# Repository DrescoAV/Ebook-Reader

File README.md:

# OpenBook Reader  
**Autor:** Andrei-Valerian Andreescu  
**Grupa:** 335CC  

## Diagrama bloc

---

## Bill Of  Materials (BOM)
| Component Name                            | Link                                                                                                   | Datasheet Link                                                                                           |
|------------------------------------------|-------------------------------------------------------------------------------------------------------------|-----------------------------------------------------------------------------------------------------------|
| 112ATAARR03ATTEND                        | [Link](https://store.comet.srl.ro/Catalogue/Product/43497/)                                                 | [Link](https://www.attend.com.tw/data/download/file/112A-TAAR-R03.rar)                                   |
| ADAFRUIT_CHIP-LED0603                    | [Link](https://www.snapeda.com/parts/KP-1608SURCK/Kingbright/view-part/?ref=search&t=LED%200603)            | [Link](https://www.snapeda.com/parts/KP-1608SURCK/Kingbright/datasheet/)                                 |
| CAPCP3225X100N                           | [Link](https://www.snapeda.com/parts/CPH3225A/Seiko+Instruments/view-part/?ref=eda)                         | [Link](https://www.snapeda.com/parts/CPH3225A/Seiko%20Instruments/datasheet/)                            |
| DIOC1608X36N                             | [Link](https://www.snapeda.com/parts/PGB1010603MR/Littelfuse/view-part/?ref=eda)                            | [Link](https://www.snapeda.com/parts/PGB1010603MR/Littelfuse%20Inc./datasheet/)                          |
| EAGLE-LTSPICE_C0402                      | [Link](https://componentsearchengine.com/part-view/CC0402MRX5R5BB106/YAGEO)                                 | [Link](https://componentsearchengine.com/Datasheets/2/CC0402MRX5R5BB106.pdf)                              |
| ESP32_WROVER_AVX---SD0805S020S1R0_AVX_0  | [Link](https://ro.mouser.com/ProductDetail/KYOCERA-AVX/SD0805S020S1R0?qs=jCA%252BPfw4LHbpkAoSnwrdjw%3D%3D)  | [Link](https://ro.mouser.com/datasheet/2/40/schottky-3165252.pdf)                                        |
| ESP32_WROVER_BME680_PSON80P300X300X100-8N| [Link](https://www.snapeda.com/parts/BME680/Bosch/view-part/?welcome=home)                                  | [Link](https://www.snapeda.com/parts/BME680/Bosch%20Sensortec/datasheet/)                                |
| ESP32_WROVER_EAGLE-LTSPICE_C0402         | [Link](https://componentsearchengine.com/part-view/CC0402MRX5R5BB106/YAGEO)                                 | [Link](https://componentsearchengine.com/Datasheets/2/CC0402MRX5R5BB106.pdf)                              |
| ESP32_WROVER_EAGLE-LTSPICE_R0402         | [Link](https://componentsearchengine.com/part-view/R0402%201%25%20100%20K%20(RC0402FR-07100KL)/YAGEO)       | [Link](https://www.yageo.com/upload/media/product/products/datasheet/rchip/PYu-RC_Group_51_RoHS_L_12.pdf)|
| ESP32_WROVER_SPARKFUN-DISCRETESEMI_SOT23-3| [Link](https://componentsearchengine.com/part-view/DMG2305UX-7/Diodes%20Incorporated)                      | [Link](https://www.diodes.com//assets/Datasheets/DMG2305UX.pdf)                                          |
| ESP32_WROVER_SPARKFUN-IC-POWER_SOT23-5   | [Link](https://ro.mouser.com/ProductDetail/Microchip-Technology/MCP73831T-5ACI-OT?qs=hH%252BOa0VZEiAcgAcEkuamXg%3D%3D) | [Link](https://ro.mouser.com/datasheet/2/268/MCP73831_Family_Data_Sheet_DS20001984H-3441711.pdf)         |
| ESP32C6_VARISTOR_CT/CN1812               | [Link](https://ro.mouser.com/ProductDetail/EPCOS-TDK/B72520T0350K062?qs=dEfas%2FXlABIszF52uu7vrg%3D%3D)     | [Link](https://www.tdk-electronics.tdk.com/inf/75/db/CTVS_14/Surge_protection_series.pdf)                |
| FH34SRJ24S05SH99                         | [Link](https://ro.mouser.com/ProductDetail/Hirose-Connector/FH34SRJ-24S-0.5SH99?qs=vcbW%252B4%252BSTIpKBl5ap9J8Fw%3D%3D) | [Link](https://ro.mouser.com/datasheet/2/185/FH34SRJ_24S_0_5SH_99__CL0580_1255_6_99_2DDrawing_0-1615044.pdf)|
| IND_4828-WE-TPC_WRE                      | [Link](https://ro.mouser.com/ProductDetail/Wurth-Elektronik/744043680?qs=PGXP4M47uW6VkZq%252BkzjrHA%3D%3D)  | [Link](https://www.we-online.com/components/products/datasheet/744043680.pdf)                            |
| JST04_1MM_RA                             | [Link](https://ro.mouser.com/ProductDetail/Adafruit/4208?qs=PzGy0jfpSMtbScLbr0L5dw%3D%3D)                   | [Link](https://ro.mouser.com/ProductDetail/Adafruit/4208?qs=PzGy0jfpSMtbScLbr0L5dw%3D%3D)                 |
| MYBUTTON                                 | [Link](https://industry.panasonic.com/global/en/products/control/switch/light-touch/number/evqpuj02k)       | [Link](https://industry.panasonic.com/global/en/downloads?tab=catalog&small_g_cd=203&part_no=EVQPUJ02K)  |
| RCL_CT3528                               | [Link](https://www.snapeda.com/parts/TAJB475K025RNJ/AVX/view-part/?t=capacitor%203528&con_ref=None)         | [Link](https://www.snapeda.com/parts/TAJB475K025RNJ/AVX/datasheet/)                                      |
| SAMACSYS_PARTS_USB4110GFA                | [Link](https://componentsearchengine.com/part-view/USB4110-GF-A/GCT%20(GLOBAL%20CONNECTOR%20TECHNOLOGY))    | [Link](https://gct.co/files/drawings/usb4110.pdf)                                                         |
| SOD3716X135N                             | [Link](https://ro.mouser.com/ProductDetail/KYOCERA-AVX/SD0805S020S1R0?qs=jCA%252BPfw4LHbpkAoSnwrdjw%3D%3D)  | [Link](https://ro.mouser.com/datasheet/2/40/schottky-3165252.pdf)                                        |
| SOIC127P1032X265-16N                     | [Link](https://eu.mouser.com/ProductDetail/Wurth-Elektronik/744043680?qs=PGXP4M47uW6VkZq%252BkzjrHA%3D%3D)  | [Link](https://www.snapeda.com/parts/DS3231SN%23/Analog%20Devices/datasheet/)                            |
| SON127P600X800X80-9N                     | [Link](https://www.snapeda.com/parts/W25Q512JVEIQ/Winbond+Electronics/view-part/?ref=eda)                   | [Link](https://www.snapeda.com/parts/W25Q512JVEIQ/Winbond%20Electronics/datasheet/)                      |
| SON50P200X200X80-9N                      | [Link](https://www.snapeda.com/parts/MAX17048G+T10/Analog+Devices/view-part/?ref=eda)                       | [Link](https://www.snapeda.com/parts/MAX17048G+T10/Analog%20Devices/datasheet/)                          |
| SOT65P210X110-3N                         | [Link](https://componentsearchengine.com/part-view/SI1308EDL-T1-GE3/Vishay)                                 | [Link](https://componentsearchengine.com/Datasheets/1/SI1308EDL-T1-GE3.pdf)                               |
| SOT95P280X125-5N                         | [Link](https://componentsearchengine.com/part-view/BD5229G-TR/ROHM%20Semiconductor)                         | [Link](https://datasheet.datasheetarchive.com/originals/distributors/Datasheets_SAMA/f2b9741ef86007909f138d561a359946.pdf) |
| SOT95P280X145-6N                         | [Link](https://www.snapeda.com/parts/USBLC6-2SC6Y/STMicroelectronics/view-part/?ref=eda)                    | [Link](https://www.snapeda.com/parts/USBLC6-2SC6Y/STMicroelectronics/datasheet/)                         |
| XCVR_ESP32-C6-WROOM-1-N8                 | [Link](https://www.snapeda.com/parts/ESP32-C6-WROOM-1-N8/Espressif+Systems/view-part/?ref=eda)              | [Link](https://www.snapeda.com/parts/ESP32-C6-WROOM-1-N8/Espressif%20Systems/datasheet/)                 |
| Screen                                   | [Link](https://grabcad.com/library/7-5in-e-ink-display-assortment-1)                                        | [Link](https://grabcad.com/library/7-5in-e-ink-display-assortment-1)                                     |
| Battery                                  | Custom Made Model                                                                                           | [Link](https://www.tme.eu/Document/e0683d8c34e6d878124489f71bffb6ee/cel0014.pdf)                          |
| Case                                     | [Download](https://ocw.cs.pub.ro/courses/_media/tsc/openbook_enclosure.zip)                                 | Not Provided                                                                                             |

---

# Descriere detaliata a functionalitatii hardware

### Componente si interfete

Proiectul utilizeaza urmatoarele componente principale:

- **ESP32-C6 WROOM**: Microcontroller principal ce gestioneaza comunicarea, procesarea datelor si interfatarea tuturor componentelor.
- **Display E-Ink Waveshare 1.5”**: Se conecteaza prin interfata SPI la ESP32, afisand informatii precum ora, data, temperatura si alte notificari.
- **SD Card Reader**: Conectat prin SPI pentru stocarea si accesarea datelor suplimentare.
- **USB-C & Charger MCP73832**: Gestioneaza incarcarea bateriei LiPo si furnizeaza alimentare stabila catre sistem.
- **Baterie LiPo**: Alimentare portabila pentru intregul sistem.
- **Senzor BME688**: Conectat prin I2C, monitorizeaza temperatura, umiditatea si calitatea aerului.
- **RTC DS3231SN**: Conectat prin I2C, mentine timpul real si data exacta chiar si fara alimentare principala.
- **Butoane GPIO**: Reset, Boot si Change pentru diverse functii si moduri operationale ale ESP32.

### Specificatii de comunicatie

- **SPI**: Utilizata pentru Display-ul E-Ink si modulul SD Card.
- **I2C**: Pentru senzorul BME688 si RTC DS3231SN.
- **GPIO**: Pentru butoane si semnale auxiliare (reset, boot).
- **USB**: Conexiune USB-C pentru incarcare si eventuala comunicare de date cu PC-ul.

### Calcul energie

- ESP32-C6: Consum activ aproximativ 100-160 mA la 3.3V
- Display E-Ink: Consum in timpul actualizarii ~15 mA, consum aproape zero in idle.
- Senzor BME688: Consum mediu 0.9 mA
- RTC DS3231SN: Consum mediu 0.2 mA
- Modul incarcare MCP73832 si circuite auxiliare: consum variabil in functie de incarcarea bateriei.

Total mediu estimat in functionare normala: ~150-200 mA la 3.3V (in actualizare), consum idle redus considerabil.

---

## Detaliere pini ESP32-C6

| Pin ESP32-C6 | Nume în schemă       | Funcție hardware          | Motivare / Utilizare                                                |
|--------------|----------------------|---------------------------|----------------------------------------------------------------------|
| GPIO0        | -                    | -                         | Nu este conectat.                                                   |
| GPIO1        | -                    | -                         | Nu este conectat.                                                   |
| GPIO2        | -                    | -                         | Nu este conectat.                                                   |
| GPIO3        | RESET                | Reset                     | Reset hardware pentru repornirea rapidă a sistemului.               |
| GPIO4        | SS_SD                | SPI CS (SD card)          | Selectează SD card-ul pentru comunicație SPI.                       |
| GPIO5        | EPD_DC               | SPI DC (Display)          | Control între date și comandă pentru e-paper display.               |
| GPIO6        | SCK                  | SPI CLK (comun)           | Semnal de ceas SPI pentru display și SD card.                       |
| GPIO7        | MOSI                 | SPI MOSI (comun)          | Trimite date către display și SD card.                              |
| GPIO8        | IO/BOOT (cu buton)   | Boot / GPIO               | Buton de boot pentru programare firmware.                           |
| GPIO9        | -                    | -                         | Nu este conectat.                                                   |
| GPIO10       | EPD_CS               | SPI CS (Display)          | Selectează e-paper display-ul pentru comunicație SPI.               |
| GPIO11       | FLASH_CS             | SPI CS (Flash)            | Selectează memoria flash externă.                                   |
| GPIO12       | USB_D-               | USB                       | Linie de date USB.                                                  |
| GPIO13       | USB_D+               | USB                       | Linie de date USB.                                                  |
| GPIO14       | IO/CHANGE            | GPIO                      | Buton pentru interacțiune utilizator (schimbare mod, etc).          |
| GPIO15       | RXD (implicit)       | UART RX                   | Recepție date serială.                                              |
| GPIO16       | TXD (implicit)       | UART TX                   | Transmisie date serială.                                            |
| GPIO17       | -                    | -                         | Nu este conectat.                                                   |
| GPIO18       | RTC_RST              | Reset RTC                 | Resetare modul RTC extern.                                          |
| GPIO19       | I2C_PW               | Alimentare I2C            | Control alimentare pentru senzori I2C.                              |
| GPIO20       | EPD_3V3_C            | Alimentare Display        | Activează alimentarea e-paper display-ului.                         |
| GPIO21       | SDA                  | I2C SDA                   | Comunicare I2C pentru senzori (ex. BME688, RTC).                    |
| GPIO22       | SCL                  | I2C SCL                   | Semnal de ceas pentru magistrala I2C.                               |
| GPIO23       | EPD_RST              | Reset Display             | Reset e-paper display.                                              |

---

## Imagini relevante

- Imagini relevante:

  - **PCB Randare**: 
  - **Carcasa si PCB (fara capac si baterie)**: 
  - **Display frontal**: 
  - **Vedere carcasa din fata**: 
  - **Carcasa deschisa**:

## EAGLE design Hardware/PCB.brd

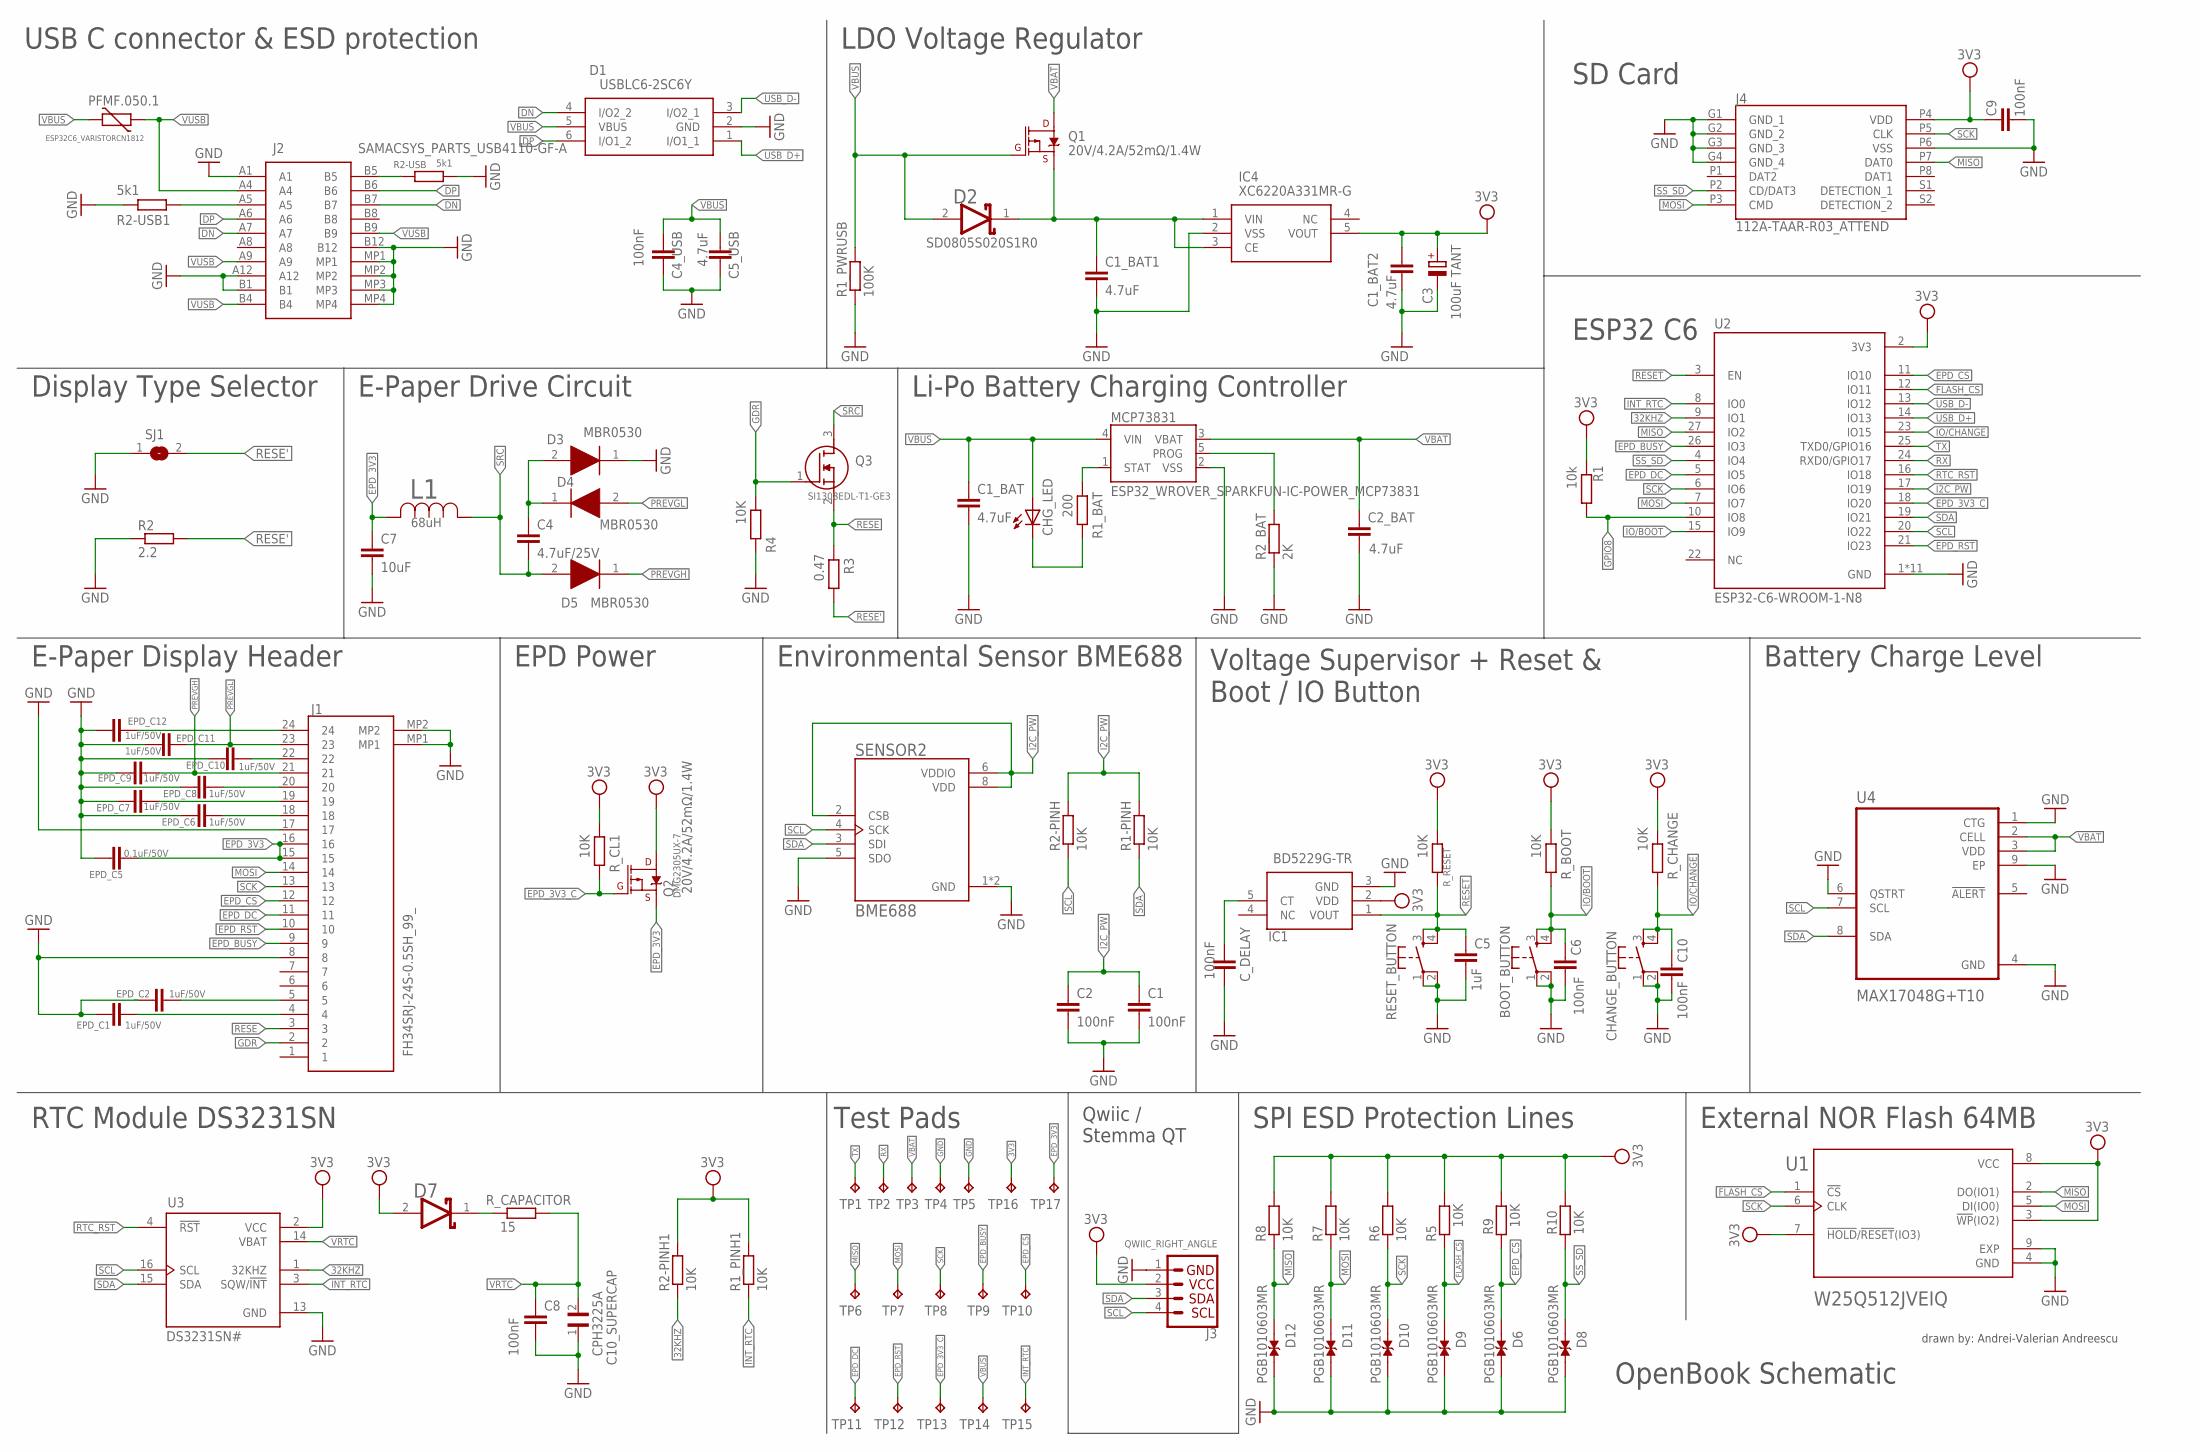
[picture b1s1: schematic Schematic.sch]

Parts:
BOOT_BUTTON: BUTTON_CUSYOMV1; MYBUTTON
C1, C2, C6, C8, C10: 100nF; ESP32_WROVER_EAGLE-LTSPICE_C0402
C1_BAT, C1_BAT1, C1_BAT2, C2_BAT, C5_USB: 4.7uF; EAGLE-LTSPICE_C0402
C3: 100uF TANT; RCL_CT3528
C4: 4.7uF/25V; ESP32_WROVER_EAGLE-LTSPICE_C0402
C4_USB, C9: 100nF; EAGLE-LTSPICE_C0402
C5: 1uF; ESP32_WROVER_EAGLE-LTSPICE_C0402
C7: 10uF; ESP32_WROVER_EAGLE-LTSPICE_C0402
C10_SUPERCAP: CPH3225A; CAPCP3225X100N
CHANGE_BUTTON: BUTTON_CUSYOMV1; MYBUTTON
CHG_LED: ADAFRUIT_LEDCHIP-LED0603; ADAFRUIT_CHIP-LED0603
C_DELAY: 100nF; ESP32_WROVER_EAGLE-LTSPICE_C0402
D1: USBLC6-2SC6Y; SOIC127P1032X265-16N
D2: SD0805S020S1R0; ESP32_WROVER_AVX---SD0805S020S1R0_AVX_SD0805S020S1R0_0
D3, D4, D5: MBR0530; SOD3716X135N
D6, D8, D9, D10, D11, D12: PGB1010603MR; DIOC1608X36N
D7: ESP32_WROVER_AVX---SD0805S020S1R0_AVX_SD0805S020S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; ESP32_WROVER_AVX---SD0805S020S1R0_AVX_SD0805S020S1R0_0
EPD_C1, EPD_C2, EPD_C6, EPD_C7, EPD_C8, EPD_C9, EPD_C10, EPD_C11, EPD_C12: 1uF/50V; ESP32_WROVER_EAGLE-LTSPICE_C0402
EPD_C5: 0.1uF/50V; ESP32_WROVER_EAGLE-LTSPICE_C0402
IC1: BD5229G-TR; SOT95P280X120-5N
IC4: XC6220A331MR-G; SOT95P280X120-5N
J1: FH34SRJ-24S-0.5SH_99_; FH34SRJ24S05SH99
J2: SAMACSYS_PARTS_USB4110-GF-A; SAMACSYS_PARTS_USB4110GFA
J3: QWIIC_RIGHT_ANGLE; JST04_1MM_RA
J4: 112A-TAAR-R03_ATTEND; 112ATAARR03ATTEND
L1: 68uH; IND_4828-WE-TPC_WRE
MCP73831: ESP32_WROVER_SPARKFUN-IC-POWER_MCP73831; ESP32_WROVER_SPARKFUN-IC-POWER_SOT23-5
PFMF.050.1: ESP32C6_VARISTORCN1812; ESP32C6_VARISTOR_CT/CN1812
Q1, Q2: 20V/4.2A/52mΩ/1.4W; ESP32_WROVER_SPARKFUN-DISCRETESEMI_SOT23-3
Q3: SI1308EDL-T1-GE3; SOT65P210X110-3N
R1: 10k; ESP32_WROVER_EAGLE-LTSPICE_R0402
R1-PINH, R1_PINH1, R2-PINH, R2-PINH1, R4, R5, R6, R7, R8, R9, R10: 10K; ESP32_WROVER_EAGLE-LTSPICE_R0402
R1_BAT: 200; ESP32_WROVER_EAGLE-LTSPICE_R0402
R1_PWRUSB: 100K; ESP32_WROVER_EAGLE-LTSPICE_R0402
R2: 2.2; ESP32_WROVER_EAGLE-LTSPICE_R0402
R2-USB, R2-USB1: 5k1; ESP32_WROVER_EAGLE-LTSPICE_R0402
R2_BAT: 2K; ESP32_WROVER_EAGLE-LTSPICE_R0402
R3: 0.47; ESP32_WROVER_EAGLE-LTSPICE_R0402
RESET_BUTTON: BUTTON_CUSYOMV1; MYBUTTON
R_BOOT: 10K; ESP32_WROVER_EAGLE-LTSPICE_R0402
R_CAPACITOR: 15; ESP32_WROVER_EAGLE-LTSPICE_R0402
R_CHANGE: 10K; ESP32_WROVER_EAGLE-LTSPICE_R0402
R_CL1: 10K; ESP32_WROVER_EAGLE-LTSPICE_R0402
R_RESET: 10K; ESP32_WROVER_EAGLE-LTSPICE_R0402
SENSOR2: BME688; ESP32_WROVER_BME680_PSON80P300X300X100-8N
SJ1: SJ
TP1, TP2, TP3, TP4, TP5, TP6, TP7, TP8, TP9, TP10, TP11, TP12, TP13, TP14, TP15, TP16, TP17: TPTP20R; TP20R
U1: W25Q512JVEIQ; SON127P600X800X80-9N
U2: ESP32-C6-WROOM-1-N8; XCVR_ESP32-C6-WROOM-1-N8
U3: DS3231SN#; SOIC127P1032X265-16N
U4: MAX17048G+T10; SON50P200X200X80-9N

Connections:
3V3: C1_BAT2.1, C3.+, C9.2, D7.2 (ANODE), IC1.2 (VDD), IC4.5 (VOUT), J3.2, J4.P4 (VDD), Q2.3 (D), R1.2, R1_PINH1.2, R2-PINH1.2, R5.2, R6.2, R7.2, R8.2, R9.2, R10.2, R_BOOT.2, R_CHANGE.2, R_CL1.2, R_RESET.2, TP16.TP, U1.3 (!WP!(IO2)), U1.7 (!HOLD!/!RESET!(IO3)), U1.8 (VCC), U2.2 (3V3), U3.2 (VCC)
32KHZ: R2-PINH1.1, U2.9 (IO1), U3.1 (32KHZ)
DN: D1.4 (I/O2_2), J2.A7, J2.B7
DP: D1.6 (I/O1_2), J2.A6, J2.B6
EPD_3V3: C7.1, EPD_C5.2, J1.15, J1.16, L1.2, Q2.2 (S), TP17.TP
EPD_3V3_C: Q2.1 (G), R_CL1.1, TP13.TP, U2.18 (IO20)
EPD_BUSY: J1.9, TP9.TP, U2.26 (IO3)
EPD_CS: D6.2, J1.12, R9.1, TP10.TP, U2.11 (IO10)
EPD_DC: J1.11, TP11.TP, U2.5 (IO5)
EPD_RST: J1.10, TP12.TP, U2.21 (IO23)
FLASH_CS: D9.2, R5.1, U1.1 (!CS), U2.12 (IO11)
GDR: J1.2, Q3.1 (G), R4.2
GND: BOOT_BUTTON.1, BOOT_BUTTON.2, C1.2, C1_BAT.2, C1_BAT1.2, C1_BAT2.2, C2.2, C2_BAT.2, C3.-, C4_USB.2, C5.2, C5_USB.2, C6.2, C7.2, C8.2, C9.1, C10.2, C10_SUPERCAP.1, CHANGE_BUTTON.1, CHANGE_BUTTON.2, C_DELAY.2, D1.2 (GND), D3.1 (K), D6.1, D8.1, D9.1, D10.1, D11.1, D12.1, EPD_C1.1, EPD_C2.1, EPD_C5.1, EPD_C6.1, EPD_C7.1, EPD_C8.1, EPD_C9.1, EPD_C10.1, EPD_C11.1, EPD_C12.1, IC1.3 (GND), IC4.2 (VSS), J1.8, J1.17, J1.MP1, J1.MP2, J2.A1, J2.A12, J2.B1, J2.B12, J2.MP1, J2.MP2, J2.MP3, J2.MP4, J3.1, J4.G1 (GND_1), J4.G2 (GND_2), J4.G3 (GND_3), J4.G4 (GND_4), J4.P6 (VSS), MCP73831.2 (VSS), R1_PWRUSB.1, R2.1, R2-USB.2, R2-USB1.1, R2_BAT.1, R4.1, RESET_BUTTON.1, RESET_BUTTON.2, SENSOR2.1 (GND), SENSOR2.5 (SDO), SENSOR2.7 (GND), SJ1.1, TP4.TP, TP5.TP, U1.4 (GND), U1.9 (EXP), U2.1 (GND), U2.28 (GND), U2.29_1 (GND), U2.29_2 (GND), U2.29_3 (GND), U2.29_4 (GND), U2.29_5 (GND), U2.29_6 (GND), U2.29_7 (GND), U2.29_8 (GND), U2.29_9 (GND), U3.13 (GND), U4.1 (CTG), U4.4 (GND), U4.6 (QSTRT), U4.9 (EP)
GPIO8: R1.1, U2.10 (IO8)
I2C_PW: C1.1, C2.1, R1-PINH.2, R2-PINH.2, SENSOR2.2 (CSB), SENSOR2.6 (VDDIO), SENSOR2.8 (VDD), U2.17 (IO19)
INT_RTC: R1_PINH1.1, TP15.TP, U2.8 (IO0), U3.3 (SQW/!INT)
IO/BOOT: BOOT_BUTTON.3, BOOT_BUTTON.4, C6.1, R_BOOT.1, U2.15 (IO9)
IO/CHANGE: C10.1, CHANGE_BUTTON.3, CHANGE_BUTTON.4, R_CHANGE.1, U2.23 (IO15)
MISO: D12.2, J4.P7 (DAT0), R8.1, TP6.TP, U1.2 (DO(IO1)), U2.27 (IO2)
MOSI: D11.2, J1.14, J4.P3 (CMD), R7.1, TP7.TP, U1.5 (DI(IO0)), U2.7 (IO7)
unnamed: C_DELAY.1, IC1.5 (CT)
unnamed: J2.A5, R2-USB1.2
unnamed: MCP73831.1 (STAT), R1_BAT.2
unnamed: C1_BAT1.1, D2.1 (CATHODE), IC4.1 (VIN), IC4.3 (CE), Q1.2 (S)
unnamed: CHG_LED.C, R1_BAT.1
unnamed: MCP73831.5 (PROG), R2_BAT.2
unnamed: EPD_C12.2, J1.24
unnamed: C4.1, D3.2 (A), D4.1 (K)
unnamed: D7.1 (CATHODE), R_CAPACITOR.1
unnamed: J2.B5, R2-USB.1
unnamed: EPD_C6.2, J1.18
unnamed: EPD_C8.2, J1.20
unnamed: EPD_C7.2, J1.19
unnamed: EPD_C10.2, J1.22
unnamed: EPD_C2.2, J1.5
unnamed: EPD_C1.2, J1.4
PREVGH: D5.1 (K), EPD_C9.2, J1.21
PREVGL: D4.2 (A), EPD_C11.2, J1.23
RESE: J1.3, Q3.2 (S), R3.2
RESE': R2.2, R3.1, SJ1.2
RESET: C5.1, IC1.1 (VOUT), RESET_BUTTON.3, RESET_BUTTON.4, R_RESET.1, U2.3 (EN)
RTC_RST: U2.16 (IO18), U3.4 (!RST)
RX: TP2.TP, U2.24 (RXD0/GPIO17)
SCK: D10.2, J1.13, J4.P5 (CLK), R6.1, TP8.TP, U1.6 (CLK), U2.6 (IO6)
SCL: J3.4, R2-PINH.1, SENSOR2.4 (SCK), U2.20 (IO22), U3.16 (SCL), U4.7 (SCL)
SDA: J3.3, R1-PINH.1, SENSOR2.3 (SDI), U2.19 (IO21), U3.15 (SDA), U4.8 (SDA)
SRC: C4.2, D5.2 (A), L1.1, Q3.3 (D)
SS_SD: D8.2, J4.P2 (CD/DAT3), R10.1, U2.4 (IO4)
TX: TP1.TP, U2.25 (TXD0/GPIO16)
USB_D+: D1.1 (I/O1_1), U2.14 (IO13)
USB_D-: D1.3 (I/O2_1), U2.13 (IO12)
VBAT: C2_BAT.1, MCP73831.3 (VBAT), Q1.3 (D), TP3.TP, U4.2 (CELL), U4.3 (VDD)
VBUS: C1_BAT.1, C4_USB.1, C5_USB.1, CHG_LED.A, D1.5 (VBUS), D2.2 (ANODE), MCP73831.4 (VIN), PFMF.050.1.2, Q1.1 (G), R1_PWRUSB.2, TP14.TP
VRTC: C8.1, C10_SUPERCAP.2, R_CAPACITOR.2, U3.14 (VBAT)
VUSB: J2.A4, J2.A9, J2.B4, J2.B9, PFMF.050.1.1

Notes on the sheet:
LDO Voltage Regulator
USB C connector & ESD protection
OpenBook Schematic
SD Card
ESP32 C6
Li-Po Battery Charging Controller
E-Paper Drive Circuit
Display Type Selector
E-Paper Display Header
EPD Power
Environmental Sensor BME688
Voltage Supervisor + Reset & Boot / IO Button
Battery Charge Level
External NOR Flash 64MB
SPI ESD Protection Lines
Qwiic / Stemma QT
Test Pads
RTC Module DS3231SN
drawn by: Andrei-Valerian Andreescu

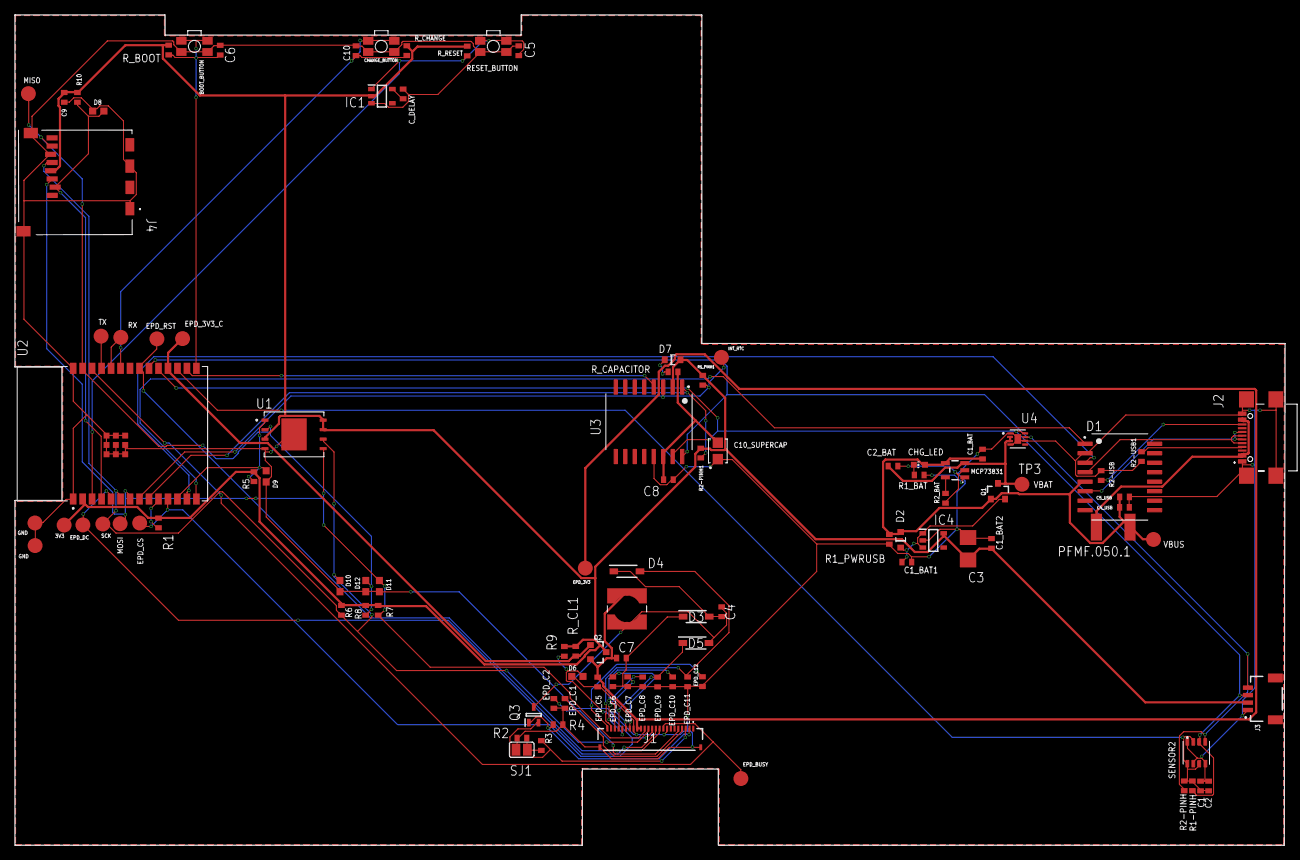
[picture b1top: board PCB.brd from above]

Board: 2 copper layers, 170.1 x 111.2 mm, 103 parts (0 on the bottom side), 55 nets.

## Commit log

2025-04-06 Done
2025-04-06 Create LICENSE
2025-04-12 Fixed #5.
2025-04-13 Fixed #6, #7, #8, #9, #12
2025-04-13 Fixed #13

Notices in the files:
parts and their libraries:
COPYRIGHT: Copyright (C) 2024 Ultra Librarian. All rights reserved.
